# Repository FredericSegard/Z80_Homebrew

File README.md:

# Z80_Homebrew
 My ZedEighty Project (Z80)

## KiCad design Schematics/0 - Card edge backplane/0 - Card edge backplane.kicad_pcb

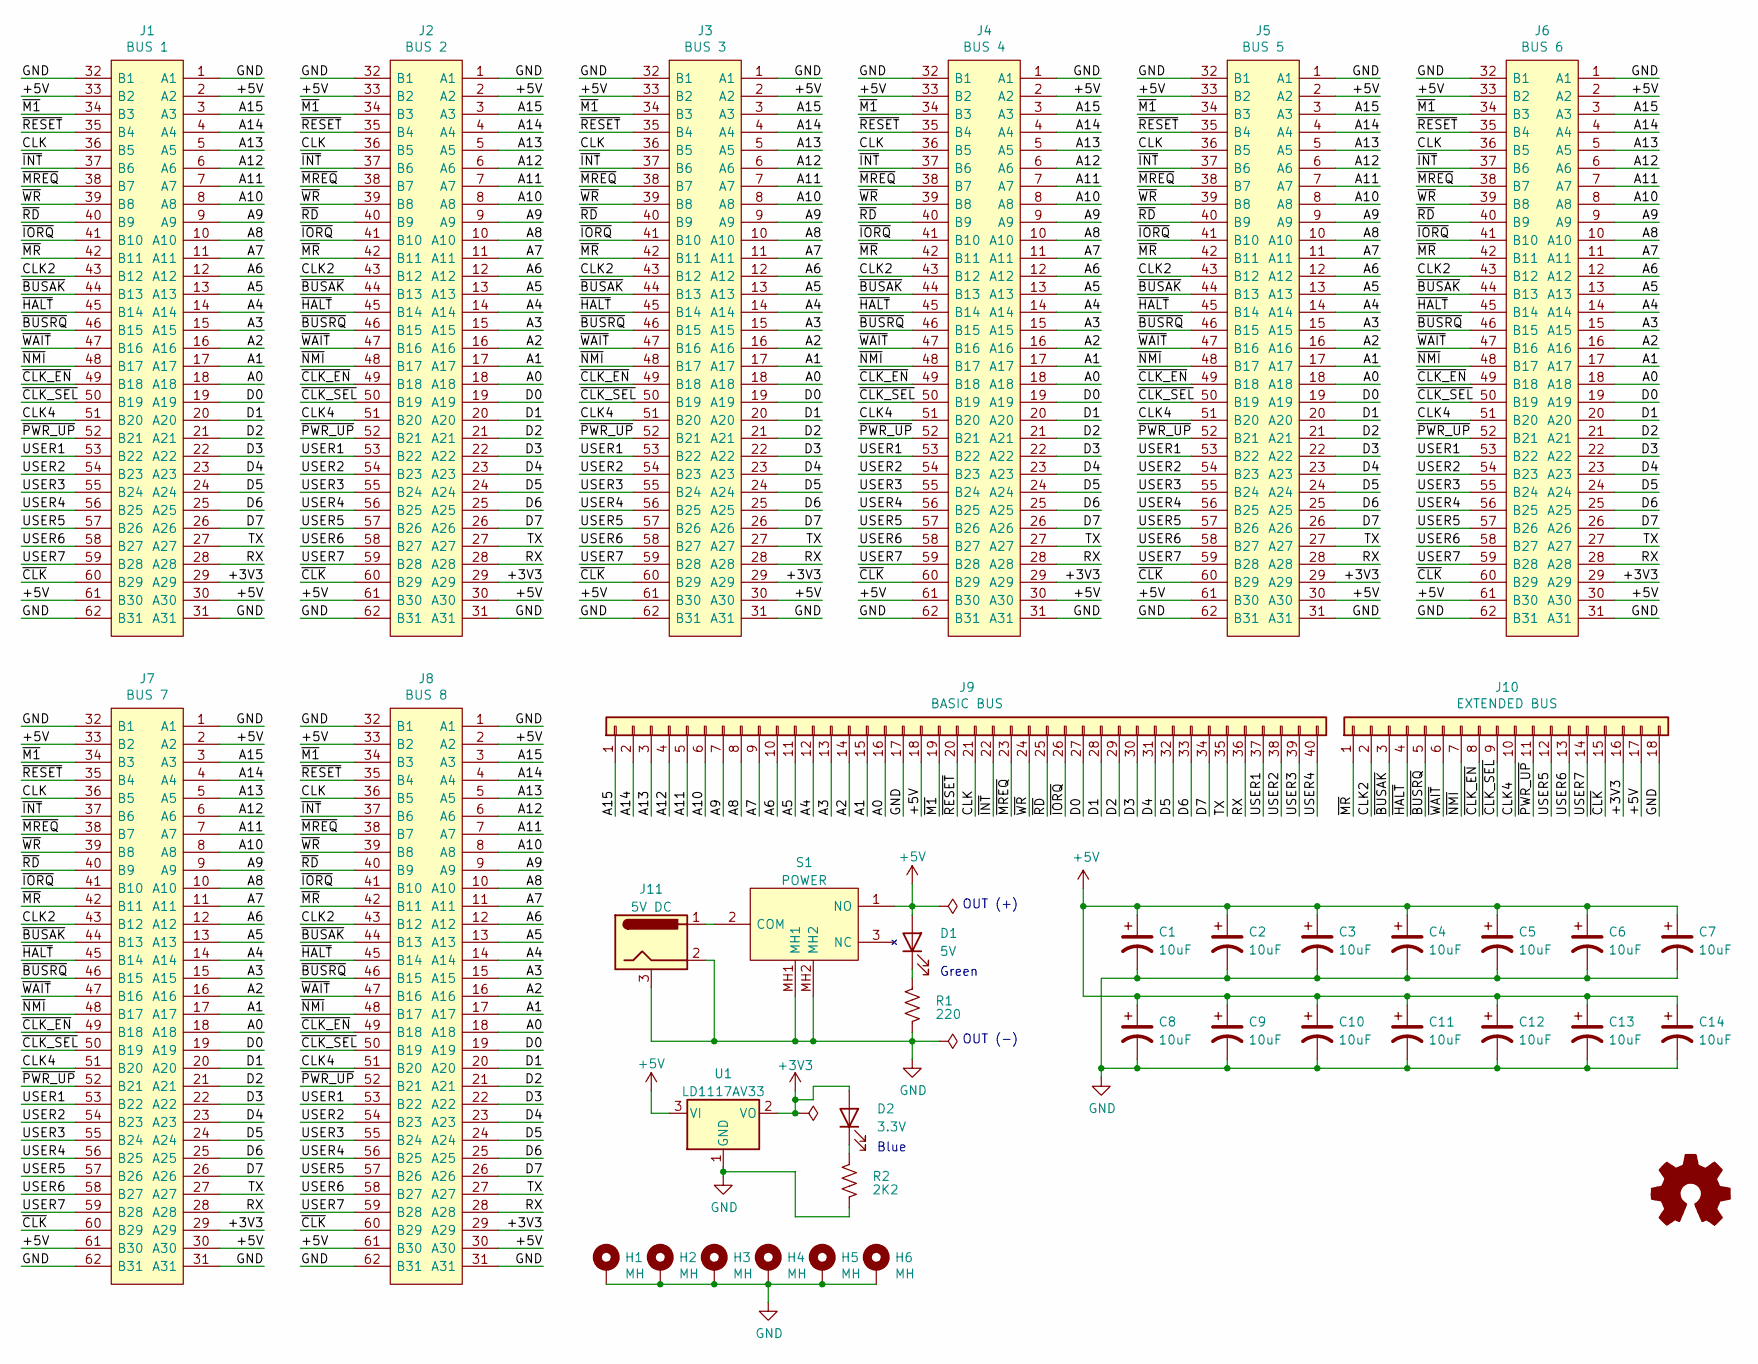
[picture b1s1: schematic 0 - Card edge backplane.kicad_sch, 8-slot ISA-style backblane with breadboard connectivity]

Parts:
C1, C2, C3, C4, C5, C6, C7, C8, C9, C10, C11, C12, C13, C14: 10uF; CP_Radial_D6.3mm_P2.50mm
D1: 5V; LED_D3.0mm
D2: 3.3V; LED_D3.0mm
H1, H2, H3, H4, H5, H6: MH; MountingHole_3.2mm_M3_Pad_Via
J1: BUS 1; ISA_Connector; Mouser Part Number 571-6-5530843-5
J2: BUS 2; ISA_Connector; Mouser Part Number 571-6-5530843-5
J3: BUS 3; ISA_Connector; Mouser Part Number 571-6-5530843-5
J4: BUS 4; ISA_Connector; Mouser Part Number 571-6-5530843-5
J5: BUS 5; ISA_Connector; Mouser Part Number 571-6-5530843-5
J6: BUS 6; ISA_Connector; Mouser Part Number 571-6-5530843-5
J7: BUS 7; ISA_Connector; Mouser Part Number 571-6-5530843-5
J8: BUS 8; ISA_Connector; Mouser Part Number 571-6-5530843-5
J9: BASIC BUS; PinHeader_1x40_P2.54mm_Vertical
J10: EXTENDED BUS; PinHeader_1x18_P2.54mm_Vertical
J11: 5V DC; BarrelJack_Horizontal
R1: 220; R_Axial_DIN0207_L6.3mm_D2.5mm_P10.16mm_Horizontal
R2: 2K2; R_Axial_DIN0207_L6.3mm_D2.5mm_P10.16mm_Horizontal
S1: POWER; SPDT_NKK_SWITCH_M2012S2A2W30; Manufacturer_Part_Number M2012S2A2W30; Mouser Part Number 633-M2012S2A2W30
U1: LD1117AV33; TO-126-3_Horizontal_TabDown

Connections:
+3V3: D2.2 (A), J1.29 (A29), J2.29 (A29), J3.29 (A29), J4.29 (A29), J5.29 (A29), J6.29 (A29), J7.29 (A29), J8.29 (A29), J10.16, U1.2 (VO)
+5V: C1.1, C2.1, C3.1, C4.1, C5.1, C6.1, C7.1, C8.1, C9.1, C10.1, C11.1, C12.1, C13.1, C14.1, D1.2 (A), J1.2 (A2), J1.30 (A30), J1.33 (B2), J1.61 (B30), J2.2 (A2), J2.30 (A30), J2.33 (B2), J2.61 (B30), J3.2 (A2), J3.30 (A30), J3.33 (B2), J3.61 (B30), J4.2 (A2), J4.30 (A30), J4.33 (B2), J4.61 (B30), J5.2 (A2), J5.30 (A30), J5.33 (B2), J5.61 (B30), J6.2 (A2), J6.30 (A30), J6.33 (B2), J6.61 (B30), J7.2 (A2), J7.30 (A30), J7.33 (B2), J7.61 (B30), J8.2 (A2), J8.30 (A30), J8.33 (B2), J8.61 (B30), J9.18, J10.17, S1.1 (NO), U1.3 (VI)
/A0: J1.18 (A18), J2.18 (A18), J3.18 (A18), J4.18 (A18), J5.18 (A18), J6.18 (A18), J7.18 (A18), J8.18 (A18), J9.16
/A1: J1.17 (A17), J2.17 (A17), J3.17 (A17), J4.17 (A17), J5.17 (A17), J6.17 (A17), J7.17 (A17), J8.17 (A17), J9.15
/A2: J1.16 (A16), J2.16 (A16), J3.16 (A16), J4.16 (A16), J5.16 (A16), J6.16 (A16), J7.16 (A16), J8.16 (A16), J9.14
/A3: J1.15 (A15), J2.15 (A15), J3.15 (A15), J4.15 (A15), J5.15 (A15), J6.15 (A15), J7.15 (A15), J8.15 (A15), J9.13
/A4: J1.14 (A14), J2.14 (A14), J3.14 (A14), J4.14 (A14), J5.14 (A14), J6.14 (A14), J7.14 (A14), J8.14 (A14), J9.12
/A5: J1.13 (A13), J2.13 (A13), J3.13 (A13), J4.13 (A13), J5.13 (A13), J6.13 (A13), J7.13 (A13), J8.13 (A13), J9.11
/A6: J1.12 (A12), J2.12 (A12), J3.12 (A12), J4.12 (A12), J5.12 (A12), J6.12 (A12), J7.12 (A12), J8.12 (A12), J9.10
/A7: J1.11 (A11), J2.11 (A11), J3.11 (A11), J4.11 (A11), J5.11 (A11), J6.11 (A11), J7.11 (A11), J8.11 (A11), J9.9
/A8: J1.10 (A10), J2.10 (A10), J3.10 (A10), J4.10 (A10), J5.10 (A10), J6.10 (A10), J7.10 (A10), J8.10 (A10), J9.8
/A9: J1.9 (A9), J2.9 (A9), J3.9 (A9), J4.9 (A9), J5.9 (A9), J6.9 (A9), J7.9 (A9), J8.9 (A9), J9.7
/A10: J1.8 (A8), J2.8 (A8), J3.8 (A8), J4.8 (A8), J5.8 (A8), J6.8 (A8), J7.8 (A8), J8.8 (A8), J9.6
/A11: J1.7 (A7), J2.7 (A7), J3.7 (A7), J4.7 (A7), J5.7 (A7), J6.7 (A7), J7.7 (A7), J8.7 (A7), J9.5
/A12: J1.6 (A6), J2.6 (A6), J3.6 (A6), J4.6 (A6), J5.6 (A6), J6.6 (A6), J7.6 (A6), J8.6 (A6), J9.4
/A13: J1.5 (A5), J2.5 (A5), J3.5 (A5), J4.5 (A5), J5.5 (A5), J6.5 (A5), J7.5 (A5), J8.5 (A5), J9.3
/A14: J1.4 (A4), J2.4 (A4), J3.4 (A4), J4.4 (A4), J5.4 (A4), J6.4 (A4), J7.4 (A4), J8.4 (A4), J9.2
/A15: J1.3 (A3), J2.3 (A3), J3.3 (A3), J4.3 (A3), J5.3 (A3), J6.3 (A3), J7.3 (A3), J8.3 (A3), J9.1
/CLK: J1.36 (B5), J2.36 (B5), J3.36 (B5), J4.36 (B5), J5.36 (B5), J6.36 (B5), J7.36 (B5), J8.36 (B5), J9.21
/CLK2: J1.43 (B12), J2.43 (B12), J3.43 (B12), J4.43 (B12), J5.43 (B12), J6.43 (B12), J7.43 (B12), J8.43 (B12), J10.2
/CLK4: J1.51 (B20), J2.51 (B20), J3.51 (B20), J4.51 (B20), J5.51 (B20), J6.51 (B20), J7.51 (B20), J8.51 (B20), J10.10
/D0: J1.19 (A19), J2.19 (A19), J3.19 (A19), J4.19 (A19), J5.19 (A19), J6.19 (A19), J7.19 (A19), J8.19 (A19), J9.27
/D1: J1.20 (A20), J2.20 (A20), J3.20 (A20), J4.20 (A20), J5.20 (A20), J6.20 (A20), J7.20 (A20), J8.20 (A20), J9.28
/D2: J1.21 (A21), J2.21 (A21), J3.21 (A21), J4.21 (A21), J5.21 (A21), J6.21 (A21), J7.21 (A21), J8.21 (A21), J9.29
/D3: J1.22 (A22), J2.22 (A22), J3.22 (A22), J4.22 (A22), J5.22 (A22), J6.22 (A22), J7.22 (A22), J8.22 (A22), J9.30
/D4: J1.23 (A23), J2.23 (A23), J3.23 (A23), J4.23 (A23), J5.23 (A23), J6.23 (A23), J7.23 (A23), J8.23 (A23), J9.31
/D5: J1.24 (A24), J2.24 (A24), J3.24 (A24), J4.24 (A24), J5.24 (A24), J6.24 (A24), J7.24 (A24), J8.24 (A24), J9.32
/D6: J1.25 (A25), J2.25 (A25), J3.25 (A25), J4.25 (A25), J5.25 (A25), J6.25 (A25), J7.25 (A25), J8.25 (A25), J9.33
/D7: J1.26 (A26), J2.26 (A26), J3.26 (A26), J4.26 (A26), J5.26 (A26), J6.26 (A26), J7.26 (A26), J8.26 (A26), J9.34
/RX: J1.28 (A28), J2.28 (A28), J3.28 (A28), J4.28 (A28), J5.28 (A28), J6.28 (A28), J7.28 (A28), J8.28 (A28), J9.36
/TX: J1.27 (A27), J2.27 (A27), J3.27 (A27), J4.27 (A27), J5.27 (A27), J6.27 (A27), J7.27 (A27), J8.27 (A27), J9.35
/USER1: J1.53 (B22), J2.53 (B22), J3.53 (B22), J4.53 (B22), J5.53 (B22), J6.53 (B22), J7.53 (B22), J8.53 (B22), J9.37
/USER2: J1.54 (B23), J2.54 (B23), J3.54 (B23), J4.54 (B23), J5.54 (B23), J6.54 (B23), J7.54 (B23), J8.54 (B23), J9.38
/USER3: J1.55 (B24), J2.55 (B24), J3.55 (B24), J4.55 (B24), J5.55 (B24), J6.55 (B24), J7.55 (B24), J8.55 (B24), J9.39
/USER4: J1.56 (B25), J2.56 (B25), J3.56 (B25), J4.56 (B25), J5.56 (B25), J6.56 (B25), J7.56 (B25), J8.56 (B25), J9.40
/USER5: J1.57 (B26), J2.57 (B26), J3.57 (B26), J4.57 (B26), J5.57 (B26), J6.57 (B26), J7.57 (B26), J8.57 (B26), J10.12
/USER6: J1.58 (B27), J2.58 (B27), J3.58 (B27), J4.58 (B27), J5.58 (B27), J6.58 (B27), J7.58 (B27), J8.58 (B27), J10.13
/USER7: J1.59 (B28), J2.59 (B28), J3.59 (B28), J4.59 (B28), J5.59 (B28), J6.59 (B28), J7.59 (B28), J8.59 (B28), J10.14
/~BUSAK: J1.44 (B13), J2.44 (B13), J3.44 (B13), J4.44 (B13), J5.44 (B13), J6.44 (B13), J7.44 (B13), J8.44 (B13), J10.3
/~BUSRQ: J1.46 (B15), J2.46 (B15), J3.46 (B15), J4.46 (B15), J5.46 (B15), J6.46 (B15), J7.46 (B15), J8.46 (B15), J10.5
/~CLK_EN: J1.49 (B18), J2.49 (B18), J3.49 (B18), J4.49 (B18), J5.49 (B18), J6.49 (B18), J7.49 (B18), J8.49 (B18), J10.8
/~CLK_SEL: J1.50 (B19), J2.50 (B19), J3.50 (B19), J4.50 (B19), J5.50 (B19), J6.50 (B19), J7.50 (B19), J8.50 (B19), J10.9
/~CLK: J1.60 (B29), J2.60 (B29), J3.60 (B29), J4.60 (B29), J5.60 (B29), J6.60 (B29), J7.60 (B29), J8.60 (B29), J10.15
/~HALT: J1.45 (B14), J2.45 (B14), J3.45 (B14), J4.45 (B14), J5.45 (B14), J6.45 (B14), J7.45 (B14), J8.45 (B14), J10.4
/~INT: J1.37 (B6), J2.37 (B6), J3.37 (B6), J4.37 (B6), J5.37 (B6), J6.37 (B6), J7.37 (B6), J8.37 (B6), J9.22
/~IORQ: J1.41 (B10), J2.41 (B10), J3.41 (B10), J4.41 (B10), J5.41 (B10), J6.41 (B10), J7.41 (B10), J8.41 (B10), J9.26
/~M1: J1.34 (B3), J2.34 (B3), J3.34 (B3), J4.34 (B3), J5.34 (B3), J6.34 (B3), J7.34 (B3), J8.34 (B3), J9.19
/~MREQ: J1.38 (B7), J2.38 (B7), J3.38 (B7), J4.38 (B7), J5.38 (B7), J6.38 (B7), J7.38 (B7), J8.38 (B7), J9.23
/~MR: J1.42 (B11), J2.42 (B11), J3.42 (B11), J4.42 (B11), J5.42 (B11), J6.42 (B11), J7.42 (B11), J8.42 (B11), J10.1
/~NMI: J1.48 (B17), J2.48 (B17), J3.48 (B17), J4.48 (B17), J5.48 (B17), J6.48 (B17), J7.48 (B17), J8.48 (B17), J10.7
/~PWR_UP: J1.52 (B21), J2.52 (B21), J3.52 (B21), J4.52 (B21), J5.52 (B21), J6.52 (B21), J7.52 (B21), J8.52 (B21), J10.11
/~RD: J1.40 (B9), J2.40 (B9), J3.40 (B9), J4.40 (B9), J5.40 (B9), J6.40 (B9), J7.40 (B9), J8.40 (B9), J9.25
/~RESET: J1.35 (B4), J2.35 (B4), J3.35 (B4), J4.35 (B4), J5.35 (B4), J6.35 (B4), J7.35 (B4), J8.35 (B4), J9.20
/~WAIT: J1.47 (B16), J2.47 (B16), J3.47 (B16), J4.47 (B16), J5.47 (B16), J6.47 (B16), J7.47 (B16), J8.47 (B16), J10.6
/~WR: J1.39 (B8), J2.39 (B8), J3.39 (B8), J4.39 (B8), J5.39 (B8), J6.39 (B8), J7.39 (B8), J8.39 (B8), J9.24
GND: C1.2, C2.2, C3.2, C4.2, C5.2, C6.2, C7.2, C8.2, C9.2, C10.2, C11.2, C12.2, C13.2, C14.2, H1.1, H2.1, H3.1, H4.1, H5.1, H6.1, J1.1 (A1), J1.31 (A31), J1.32 (B1), J1.62 (B31), J2.1 (A1), J2.31 (A31), J2.32 (B1), J2.62 (B31), J3.1 (A1), J3.31 (A31), J3.32 (B1), J3.62 (B31), J4.1 (A1), J4.31 (A31), J4.32 (B1), J4.62 (B31), J5.1 (A1), J5.31 (A31), J5.32 (B1), J5.62 (B31), J6.1 (A1), J6.31 (A31), J6.32 (B1), J6.62 (B31), J7.1 (A1), J7.31 (A31), J7.32 (B1), J7.62 (B31), J8.1 (A1), J8.31 (A31), J8.32 (B1), J8.62 (B31), J9.17, J10.18, J11.2, J11.3, R1.1, R2.1, S1.MH1, S1.MH2, U1.1 (GND)
unnamed: D1.1 (K), R1.2
unnamed: D2.1 (K), R2.2
unnamed: J11.1, S1.2 (COM)

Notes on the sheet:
OUT (+)
Blue
Green
OUT (-)

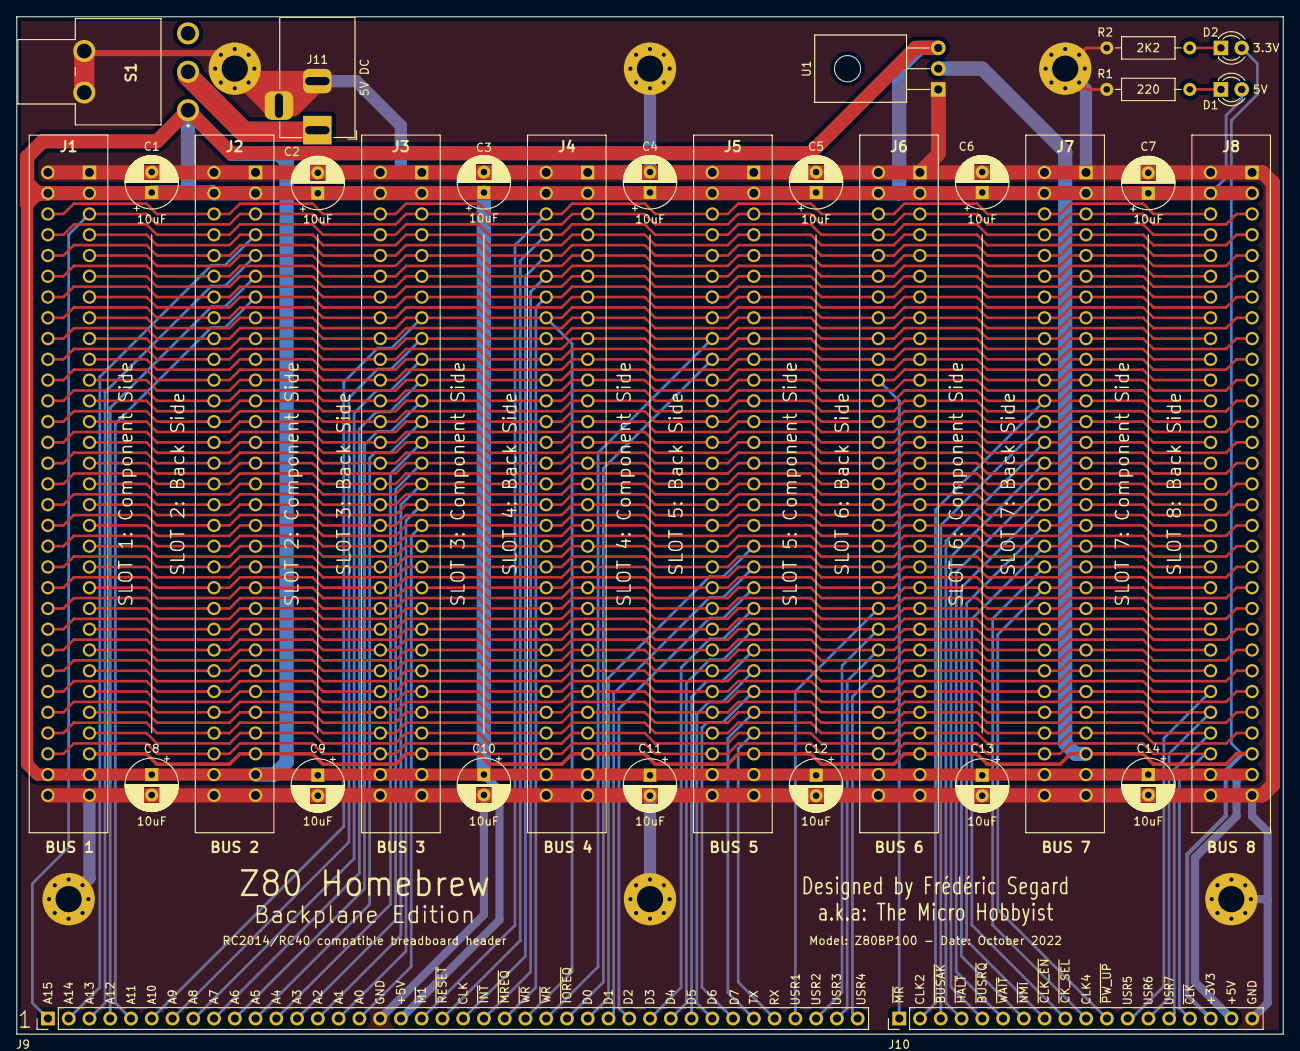
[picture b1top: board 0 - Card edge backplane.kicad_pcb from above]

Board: 2 copper layers, 154.9 x 124.5 mm, 37 parts (0 on the bottom side), 59 nets.

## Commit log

2023-02-27 Basic modifications
